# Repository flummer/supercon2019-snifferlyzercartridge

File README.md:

# Snifferlyzer Cartridge for the 2019 Hackaday Superconference Badge

The Snifferlyzer is a simple cartridge that provides a buffered input to allow logic analyzer functionality. It's using the OnSemi 74LCX16245, that has 5V tolerant inputs and the configuration pins for the transceiver is also hooked up to the badge, allowing full control over the direction of the two 8bit banks.

This cartridge is based on the [unofficial Superconference 2019 Badge Cartridge template](https://github.com/flummer/supercon2019-cartridgetemplate) and hence include the w25q128 SPI flash and a 100nF cap in addition to the 2x20 pin angled male pin header for the badge connection. The flash allows badge configurations and firmware specific to this cartridge to be loaded from the cartridge it self making it selfcontained.

## Version 1.2 update

This updated version fixes an error in the pin connections on the cartridge connector (the two columns was flipped for some signals).

## Special note about the original version

If you want to use a PCB based on the original version with incorrect connections, it is possible to make a hardware hack on the 20x2 angeled header, where you move the pins around and bend some of them a bit, very precisely.

## License

The contents of this repository is released under the following licence:

 * the "Creative Commons Attribution-ShareAlike 4.0 International License"
   (CC BY-SA 4.0) full text of this license is included in the LICENSE file
   and a copy can also be found at
   http://creativecommons.org/licenses/by-sa/4.0/

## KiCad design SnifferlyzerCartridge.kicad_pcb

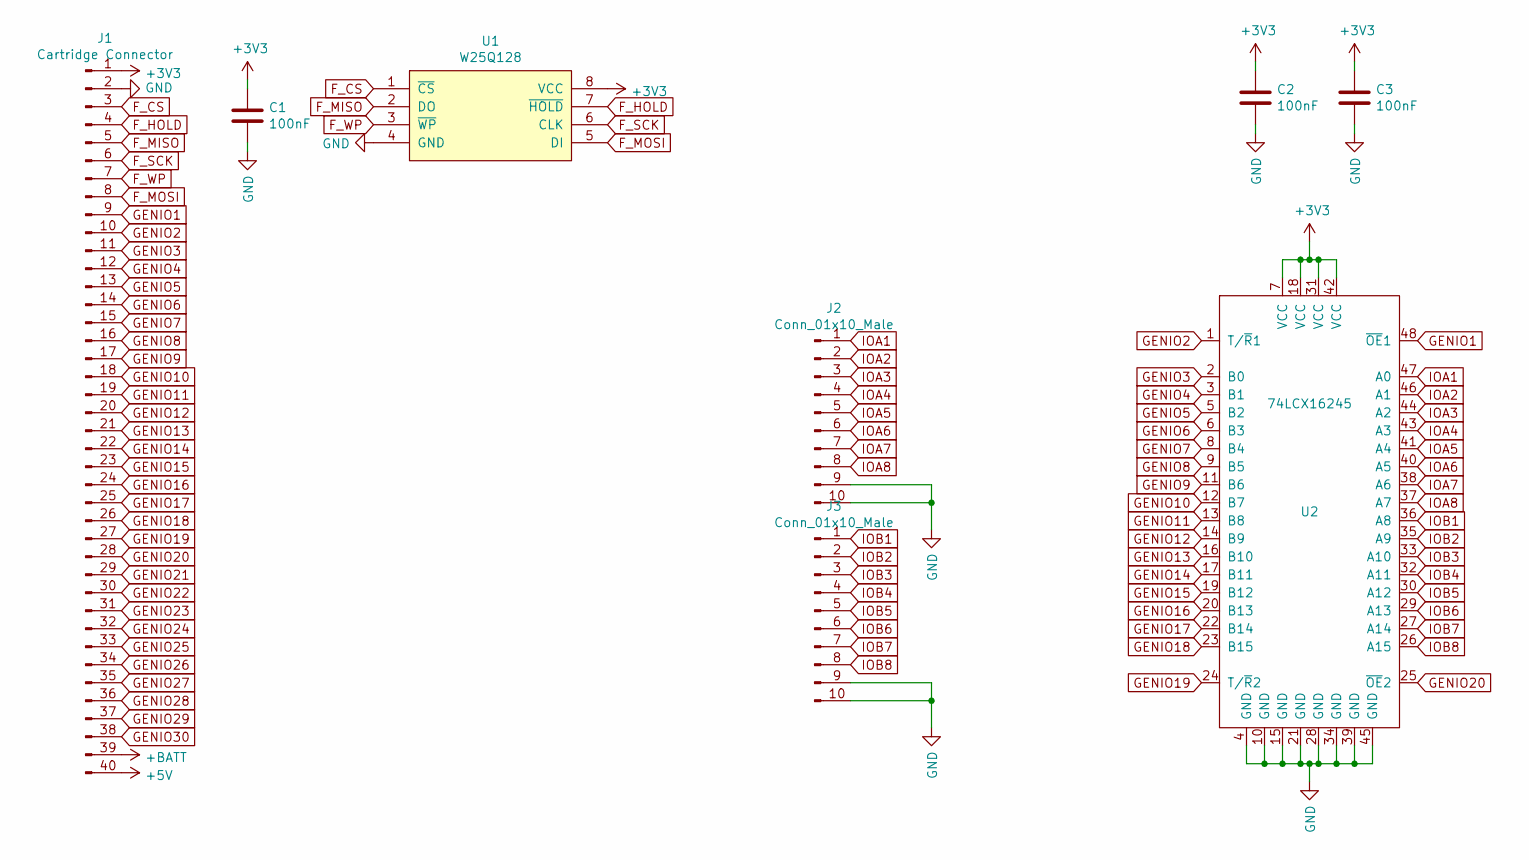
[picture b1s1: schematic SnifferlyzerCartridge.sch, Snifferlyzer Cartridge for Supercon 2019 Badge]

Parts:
C1, C2, C3: 100nF; C_0805_HandSoldering
J1: Cartridge Connector; Supercon_Cartridge_40pin_Connector
J2, J3: Conn_01x10_Male; Pin_Header_Angled_1x10_Pitch2.54mm
U1: W25Q128; SO-8_5.3x6.2mm_Pitch1.27mm
U2: 74LCX16245; TSSOP-48_6.1x12.5mm_Pitch0.5mm

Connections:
+3V3: C1.1, C2.1, C3.1, J1.1, U1.8 (VCC), U2.7 (VCC), U2.18 (VCC), U2.31 (VCC), U2.42 (VCC)
+5V: J1.40
+BATT: J1.39
F_CS: J1.3, U1.1 (~CS)
F_HOLD: J1.4, U1.7 (~HOLD)
F_MISO: J1.5, U1.2 (DO)
F_MOSI: J1.8, U1.5 (DI)
F_SCK: J1.6, U1.6 (CLK)
F_WP: J1.7, U1.3 (~WP)
GENIO1: J1.9, U2.48 (~OE~1)
GENIO2: J1.10, U2.1 (T/~R~1)
GENIO3: J1.11, U2.2 (B0)
GENIO4: J1.12, U2.3 (B1)
GENIO5: J1.13, U2.5 (B2)
GENIO6: J1.14, U2.6 (B3)
GENIO7: J1.15, U2.8 (B4)
GENIO8: J1.16, U2.9 (B5)
GENIO9: J1.17, U2.11 (B6)
GENIO10: J1.18, U2.12 (B7)
GENIO11: J1.19, U2.13 (B8)
GENIO12: J1.20, U2.14 (B9)
GENIO13: J1.21, U2.16 (B10)
GENIO14: J1.22, U2.17 (B11)
GENIO15: J1.23, U2.19 (B12)
GENIO16: J1.24, U2.20 (B13)
GENIO17: J1.25, U2.22 (B14)
GENIO18: J1.26, U2.23 (B15)
GENIO19: J1.27, U2.24 (T/~R~2)
GENIO20: J1.28, U2.25 (~OE~2)
GENIO21: J1.29
GENIO22: J1.30
GENIO23: J1.31
GENIO24: J1.32
GENIO25: J1.33
GENIO26: J1.34
GENIO27: J1.35
GENIO28: J1.36
GENIO29: J1.37
GENIO30: J1.38
GND: C1.2, C2.2, C3.2, J1.2, J2.9, J2.10, J3.9, J3.10, U1.4 (GND), U2.4 (GND), U2.10 (GND), U2.15 (GND), U2.21 (GND), U2.28 (GND), U2.34 (GND), U2.39 (GND), U2.45 (GND)
IOA1: J2.1, U2.47 (A0)
IOA2: J2.2, U2.46 (A1)
IOA3: J2.3, U2.44 (A2)
IOA4: J2.4, U2.43 (A3)
IOA5: J2.5, U2.41 (A4)
IOA6: J2.6, U2.40 (A5)
IOA7: J2.7, U2.38 (A6)
IOA8: J2.8, U2.37 (A7)
IOB1: J3.1, U2.36 (A8)
IOB2: J3.2, U2.35 (A9)
IOB3: J3.3, U2.33 (A10)
IOB4: J3.4, U2.32 (A11)
IOB5: J3.5, U2.30 (A12)
IOB6: J3.6, U2.29 (A13)
IOB7: J3.7, U2.27 (A14)
IOB8: J3.8, U2.26 (A15)

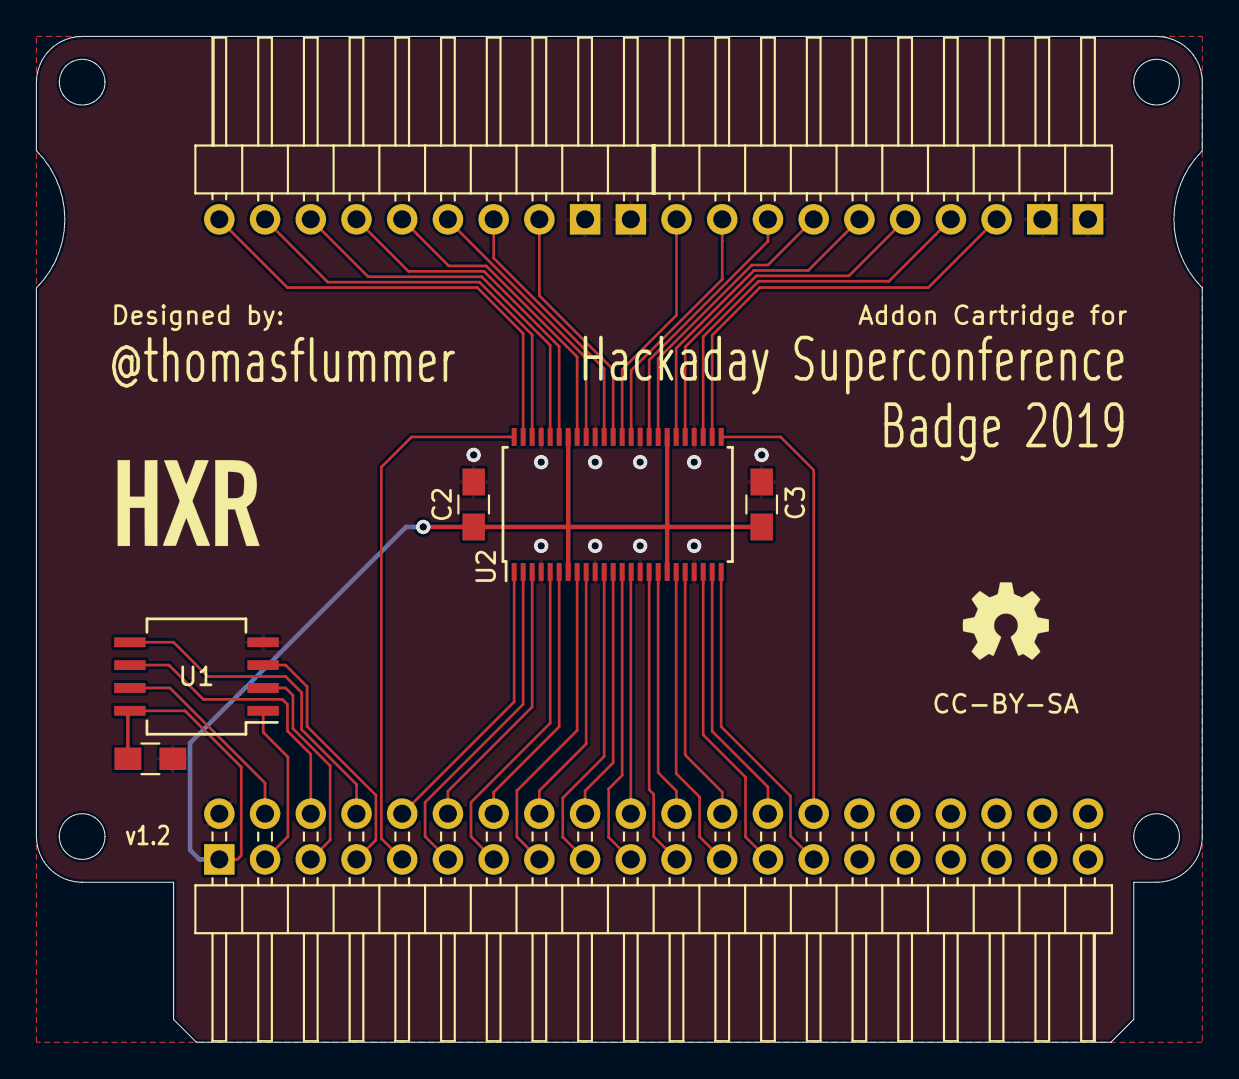
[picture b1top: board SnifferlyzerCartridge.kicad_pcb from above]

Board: 2 copper layers, 64.8 x 55.9 mm, 8 parts (0 on the bottom side), 44 nets.

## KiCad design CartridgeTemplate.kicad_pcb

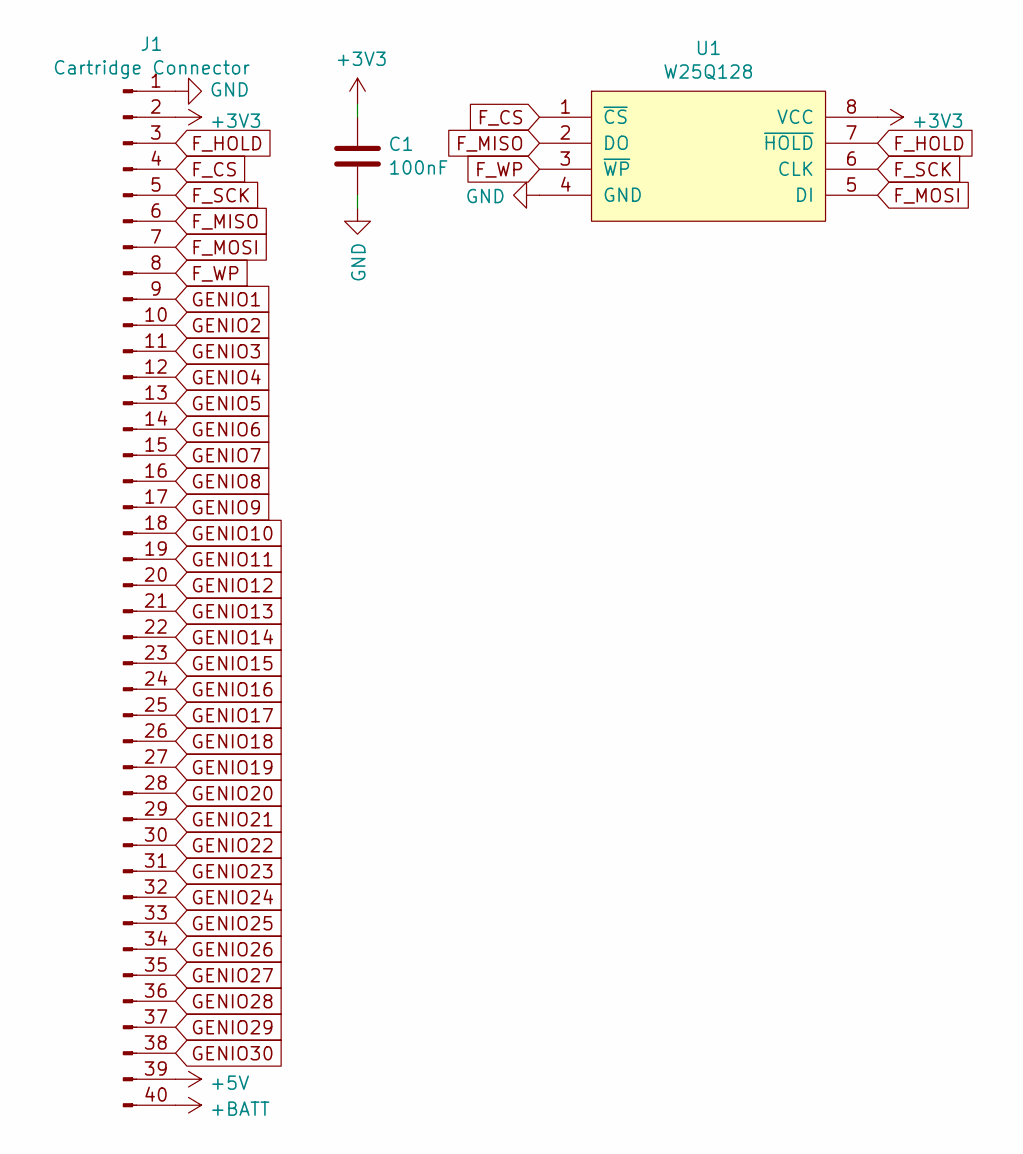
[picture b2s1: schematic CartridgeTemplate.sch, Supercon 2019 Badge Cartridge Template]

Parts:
C1: 100nF; C_0805_HandSoldering
J1: Cartridge Connector; Supercon_Cartridge_40pin_Connector
U1: W25Q128; SO-8_5.3x6.2mm_Pitch1.27mm

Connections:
+3V3: C1.1, J1.2, U1.8 (VCC)
+5V: J1.39
+BATT: J1.40
F_CS: J1.4, U1.1 (~CS)
F_HOLD: J1.3, U1.7 (~HOLD)
F_MISO: J1.6, U1.2 (DO)
F_MOSI: J1.7, U1.5 (DI)
F_SCK: J1.5, U1.6 (CLK)
F_WP: J1.8, U1.3 (~WP)
GENIO1: J1.9
GENIO2: J1.10
GENIO3: J1.11
GENIO4: J1.12
GENIO5: J1.13
GENIO6: J1.14
GENIO7: J1.15
GENIO8: J1.16
GENIO9: J1.17
GENIO10: J1.18
GENIO11: J1.19
GENIO12: J1.20
GENIO13: J1.21
GENIO14: J1.22
GENIO15: J1.23
GENIO16: J1.24
GENIO17: J1.25
GENIO18: J1.26
GENIO19: J1.27
GENIO20: J1.28
GENIO21: J1.29
GENIO22: J1.30
GENIO23: J1.31
GENIO24: J1.32
GENIO25: J1.33
GENIO26: J1.34
GENIO27: J1.35
GENIO28: J1.36
GENIO29: J1.37
GENIO30: J1.38
GND: C1.2, J1.1, U1.4 (GND)

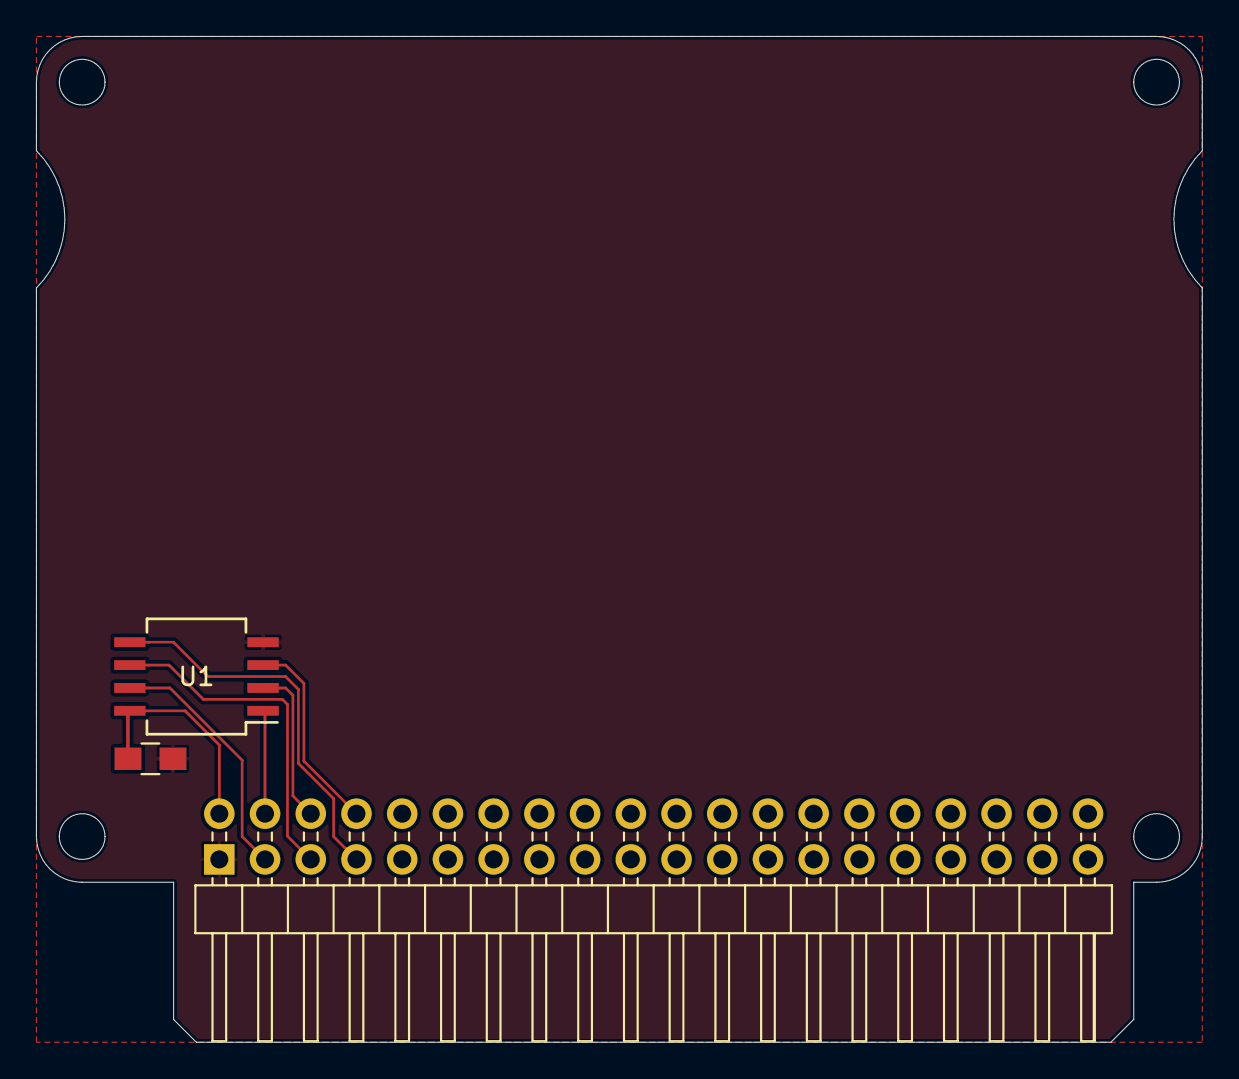
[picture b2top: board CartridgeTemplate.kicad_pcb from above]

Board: 2 copper layers, 64.8 x 55.9 mm, 3 parts (0 on the bottom side), 8 nets.

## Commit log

2019-10-26 Renamed template files and updated README
2019-10-26 First design of the Snifferlyzer cartridge
    Also updated:
    - README
    - Render image
    - .gitignore
2019-10-29 Updated README and gerber export settings
2019-11-16 Fixed error in cartridge connector pin assignments
    Updated to version 1.2
